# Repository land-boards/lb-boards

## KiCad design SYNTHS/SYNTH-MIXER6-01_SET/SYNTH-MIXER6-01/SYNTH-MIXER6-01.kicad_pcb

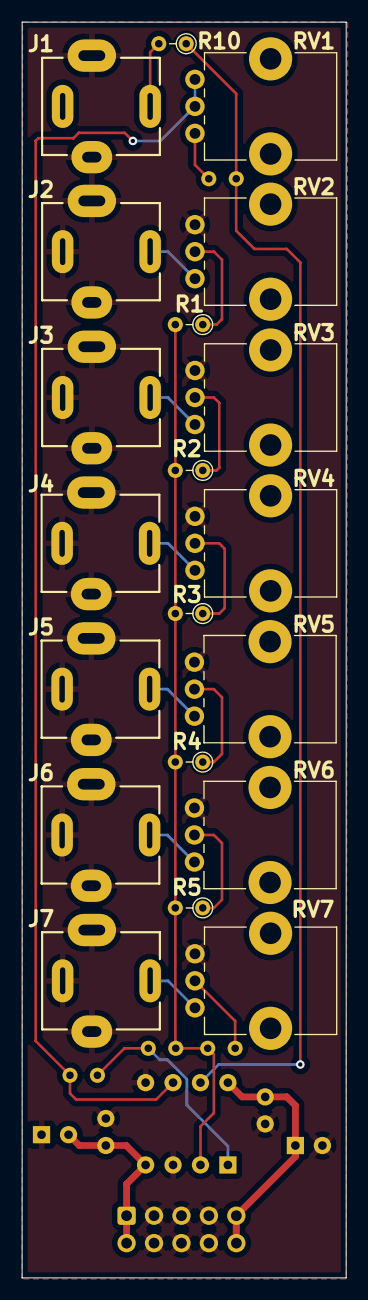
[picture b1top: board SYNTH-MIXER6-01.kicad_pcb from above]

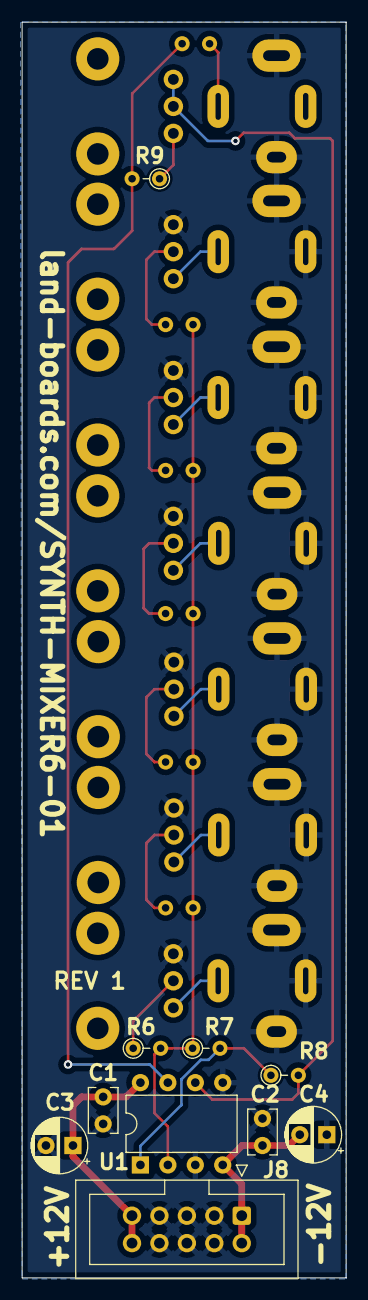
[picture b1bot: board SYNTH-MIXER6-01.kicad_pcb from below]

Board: 2 copper layers, 30.0 x 116.2 mm, 30 parts (10 on the bottom side), 21 nets.

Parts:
C1, C2: 0.1uF; C_Rect_L4.0mm_W2.5mm_P2.50mm
C3, C4: 10uF; CP_Radial_D5.0mm_P2.50mm
J1, J2, J3, J4, J5, J6, J7: PJ-301BM; Jack_3.5mm_QingPu_WQP-PJ301BM_Vertical
J8: Conn_02x05; IDC-Header_2x05_P2.54mm_Vertical
R1, R2, R3, R4, R5, R6, R7: 100K; R_Axial_DIN0204_L3.6mm_D1.6mm_P2.54mm_Vertical
R8: 22K; R_Axial_DIN0204_L3.6mm_D1.6mm_P2.54mm_Vertical
R9: 4.7K; R_Axial_DIN0204_L3.6mm_D1.6mm_P2.54mm_Vertical
R10: 1K; R_Axial_DIN0204_L3.6mm_D1.6mm_P2.54mm_Vertical
RV1, RV2, RV3, RV4, RV5, RV6, RV7: 10K; Potentiometer_Bourns_PTV09A-1_Single_Vertical
U1: TL072; DIP-8_W7.62mm

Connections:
+12V: C1.1, C3.1, J8.9, J8.10, U1.8 (V+)
-12V: C2.2, C4.2, J8.1, J8.2, U1.4 (V-)
/OUT: J1.T, R10.2
/POTWIPER_1: R1.1, RV2.2
/POTWIPER_2: R2.1, RV3.2
/POTWIPER_3: R3.1, RV4.2
/POTWIPER_4: R4.1, RV5.2
/POTWIPER_5: R5.1, RV6.2
/POTWIPER_6: R6.1, RV7.2
/VI_1: J2.T, RV2.1
/VI_2: J3.T, RV3.1
/VI_3: J4.T, RV4.1
/VI_4: J5.T, RV5.1
/VI_5: J6.T, RV6.1
/VI_6: J7.T, RV7.1
/VO: R9.2, R10.1, U1.7
/VOL1: R9.1, RV1.1
/VOL2: R8.2, RV1.2, RV1.3, U1.6 (-)
/VSUM: R1.2, R2.2, R3.2, R4.2, R5.2, R6.2, R7.1, U1.2 (-)
GND: C1.2, C2.1, C3.2, C4.1, J1.S, J2.S, J2.TN, J3.S, J3.TN, J4.S, J4.TN, J5.S, J5.TN, J6.S, J6.TN, J7.S, J7.TN, J8.3, J8.4, J8.5, J8.6, J8.7, J8.8, RV2.3, RV3.3, RV4.3, RV5.3, RV6.3, RV7.3, U1.3 (+), U1.5 (+)
unnamed: R7.2, R8.1, U1.1

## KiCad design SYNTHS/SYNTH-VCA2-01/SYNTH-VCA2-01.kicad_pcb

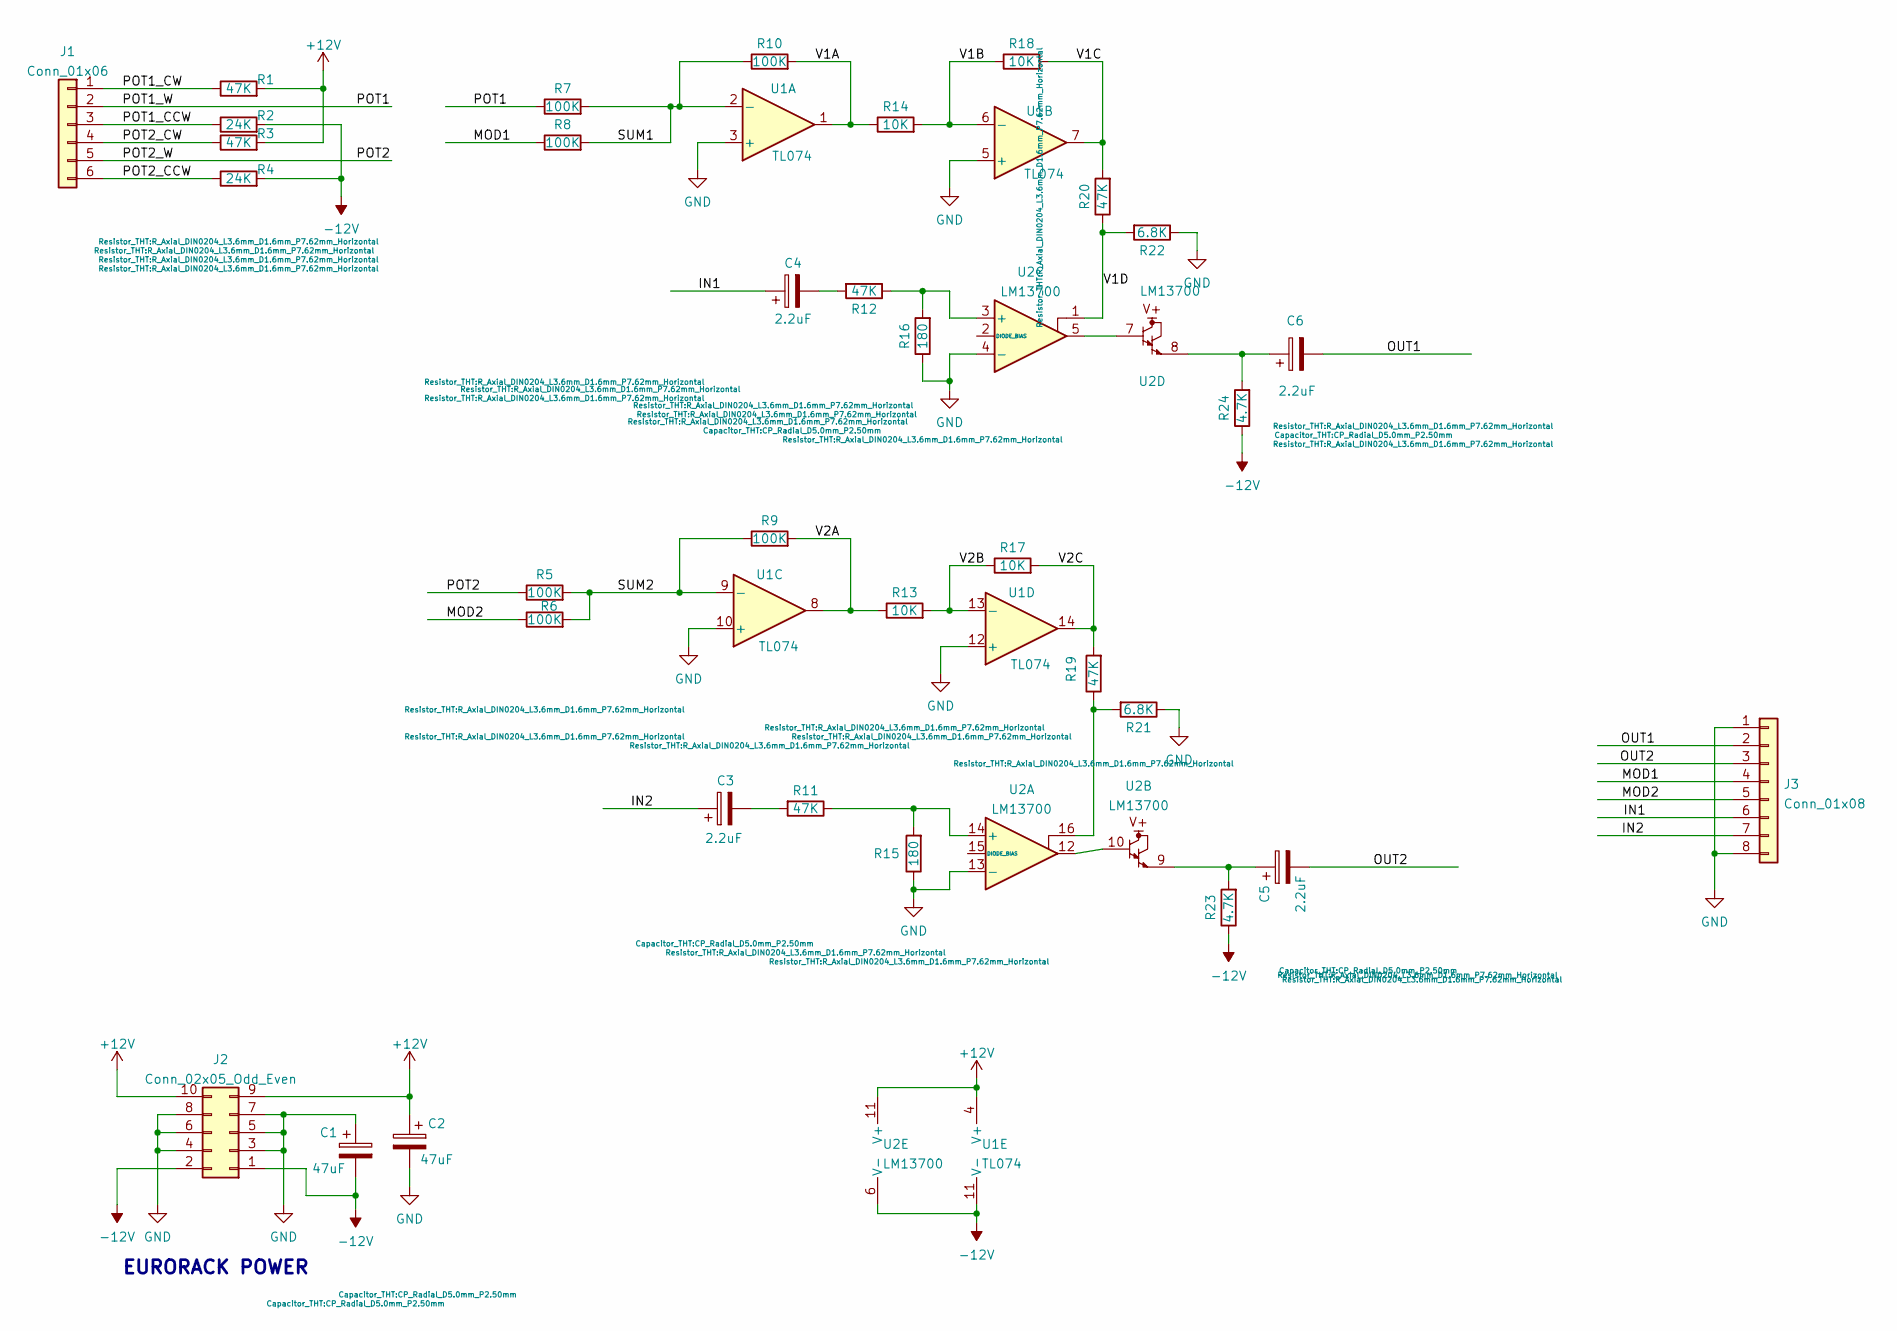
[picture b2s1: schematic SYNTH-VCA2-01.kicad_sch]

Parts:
C1, C2: 47uF; CP_Radial_D5.0mm_P2.50mm
C3, C4, C5, C6: 2.2uF; CP_Radial_D5.0mm_P2.50mm
J1: Conn_01x06; PinSocket_1x06_P2.54mm_Vertical
J2: Conn_02x05_Odd_Even; IDC-Header_2x05_P2.54mm_Vertical
J3: Conn_01x08; PinSocket_1x08_P2.54mm_Vertical
R1, R3, R11, R12, R19, R20: 47K; R_Axial_DIN0204_L3.6mm_D1.6mm_P7.62mm_Horizontal
R2, R4: 24K; R_Axial_DIN0204_L3.6mm_D1.6mm_P7.62mm_Horizontal
R5, R6, R7, R8, R9, R10: 100K; R_Axial_DIN0204_L3.6mm_D1.6mm_P7.62mm_Horizontal
R13, R14, R17, R18: 10K; R_Axial_DIN0204_L3.6mm_D1.6mm_P7.62mm_Horizontal
R15, R16: 180; R_Axial_DIN0204_L3.6mm_D1.6mm_P7.62mm_Horizontal
R21, R22: 6.8K; R_Axial_DIN0204_L3.6mm_D1.6mm_P7.62mm_Horizontal
R23, R24: 4.7K; R_Axial_DIN0204_L3.6mm_D1.6mm_P7.62mm_Horizontal
U1: TL074
U2: LM13700

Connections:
+12V: C2.1, J2.9, J2.10, R1.2, R3.2, U1.4 (V+), U2.11 (V+)
-12V: C1.2, J2.1, J2.2, R2.2, R4.2, R23.1, R24.1, U1.11 (V-), U2.6 (V-)
/IN1: C4.1, J3.6
/IN2: C3.1, J3.7
/MOD1: J3.4, R8.1
/MOD2: J3.5, R6.1
/OUT1: C6.2, J3.2
/OUT2: C5.2, J3.3
/POT1: J1.2, R7.1
/POT1_CCW: J1.3, R2.1
/POT1_CW: J1.1, R1.1
/POT2: J1.5, R5.1
/POT2_CCW: J1.6, R4.1
/POT2_CW: J1.4, R3.1
/SUM1: R7.2, R8.2, R10.1, U1.2 (-)
/SUM2: R5.2, R6.2, R9.1, U1.9 (-)
/V1A: R10.2, R14.1, U1.1
/V1B: R14.2, R18.1, U1.6 (-)
/V1C: R18.2, R20.2, U1.7
/V1D: R20.1, R22.2, U2.1
/V2A: R9.2, R13.1, U1.8
/V2B: R13.2, R17.1, U1.13 (-)
/V2C: R17.2, R19.2, U1.14
GND: C1.1, C2.2, J2.3, J2.4, J2.5, J2.6, J2.7, J2.8, J3.1, J3.8, R15.1, R16.1, R21.1, R22.1, U1.3 (+), U1.5 (+), U1.10 (+), U1.12 (+), U2.4 (-), U2.13 (-)
unnamed: C3.2, R11.2
unnamed: C4.2, R12.2
unnamed: C5.1, R23.2, U2.9
unnamed: C6.1, R24.2, U2.8
unnamed: R12.1, R16.2, U2.3 (+)
unnamed: R11.1, R15.2, U2.14 (+)
unnamed: R19.1, R21.2, U2.16
unnamed: U2.5, U2.7
unnamed: U2.10, U2.12

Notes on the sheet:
EURORACK POWER

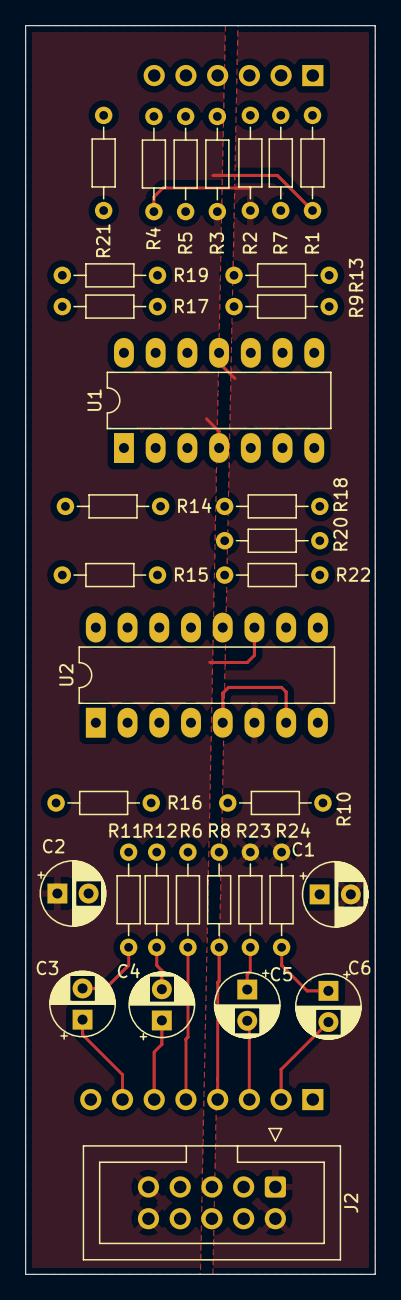
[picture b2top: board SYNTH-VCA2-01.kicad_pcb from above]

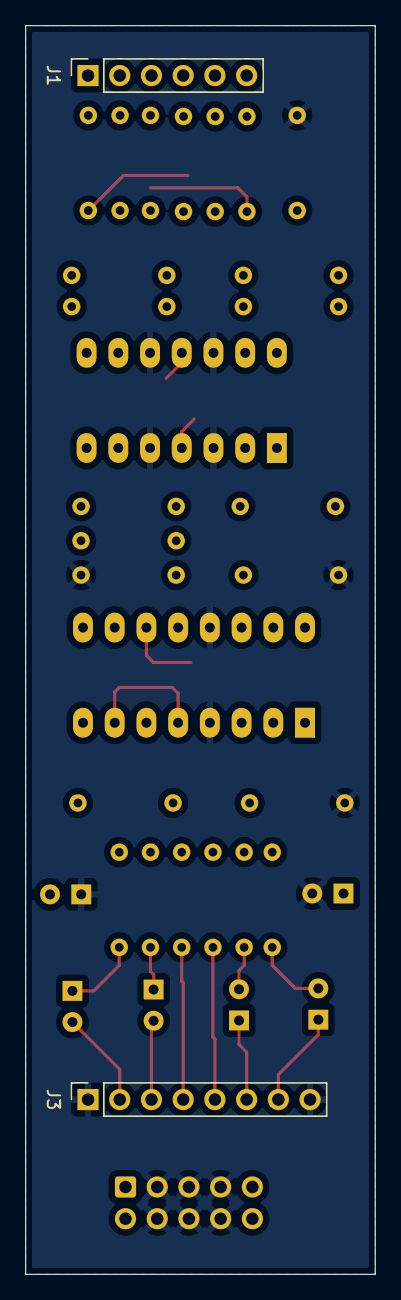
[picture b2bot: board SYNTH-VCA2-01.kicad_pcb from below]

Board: 2 copper layers, 28.0 x 100.0 mm, 35 parts (2 on the bottom side), 33 nets.

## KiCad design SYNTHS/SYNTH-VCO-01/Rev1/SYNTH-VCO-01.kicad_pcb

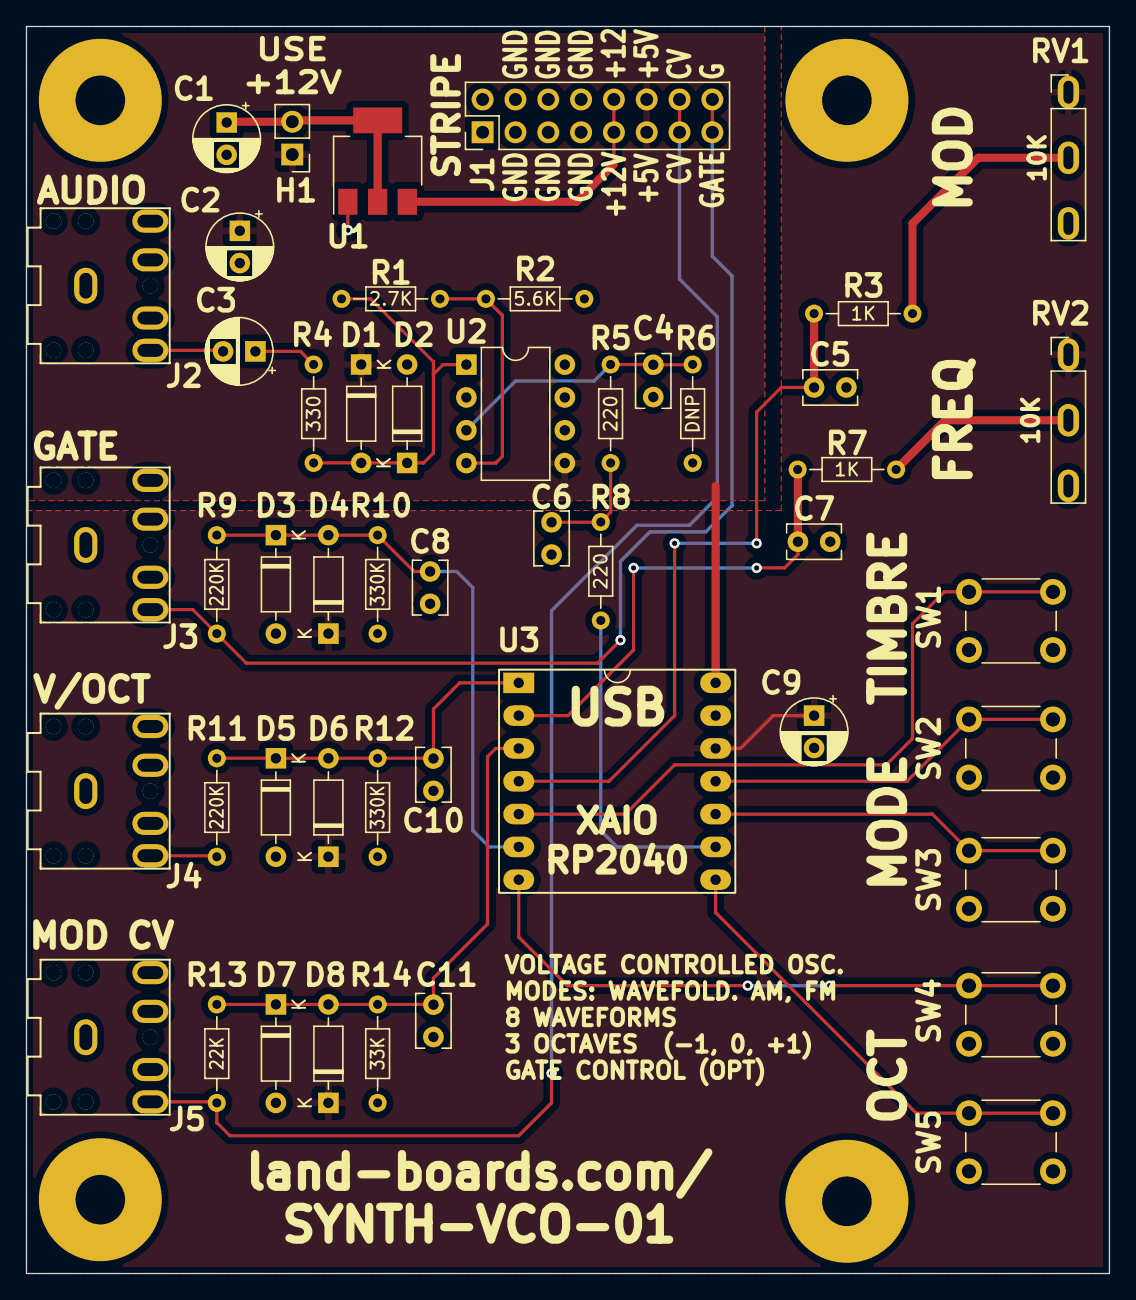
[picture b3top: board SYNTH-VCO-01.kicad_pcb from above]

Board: 2 copper layers, 83.8 x 96.5 mm, 53 parts (0 on the bottom side), 27 nets.

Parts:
C1, C2, C3, C9: 10uF; CP_Radial_D5.0mm_P2.50mm
C4, C6: 10nF; C_Rect_L4.0mm_W2.5mm_P2.50mm
C5, C7: 0.1uF; C_Rect_L4.0mm_W2.5mm_P2.50mm
C8, C10, C11: 0.01uF; C_Rect_L4.0mm_W2.5mm_P2.50mm
D1, D2, D3, D4, D5, D6, D7, D8: BAT41; D_DO-35_SOD27_P7.62mm_Horizontal
H1: Conn_01x02; PinHeader_1x02_P2.54mm_Vertical
J1: Conn_02x08_Odd_Even; PinHeader_2x08_P2.54mm_Vertical
J2, J3, J4, J5: AudioJack3; Jack_3.5mm_CUI_SJ1-3523N_Horizontal
MTG1, MTG2, MTG3, MTG4: MountingHole; MTG-6-32
R1: 2.7K; R_Axial_DIN0204_L3.6mm_D1.6mm_P7.62mm_Horizontal
R2: 5.6K; R_Axial_DIN0204_L3.6mm_D1.6mm_P7.62mm_Horizontal
R3, R7: 1K; R_Axial_DIN0204_L3.6mm_D1.6mm_P7.62mm_Horizontal
R4: 330; R_Axial_DIN0204_L3.6mm_D1.6mm_P7.62mm_Horizontal
R5, R8: 220; R_Axial_DIN0204_L3.6mm_D1.6mm_P7.62mm_Horizontal
R6: DNP; R_Axial_DIN0204_L3.6mm_D1.6mm_P7.62mm_Horizontal
R9, R11: 220K; R_Axial_DIN0204_L3.6mm_D1.6mm_P7.62mm_Horizontal
R10, R12: 330K; R_Axial_DIN0204_L3.6mm_D1.6mm_P7.62mm_Horizontal
R13: 22K; R_Axial_DIN0204_L3.6mm_D1.6mm_P7.62mm_Horizontal
R14: 33K; R_Axial_DIN0204_L3.6mm_D1.6mm_P7.62mm_Horizontal
RV1, RV2: 10K; Pot3
SW1, SW2, SW3, SW4, SW5: SW_Push; SW_PUSH_6mm_H8.5mm
U1: AZ1117-5; SOT-223
U2: MCP6232; DIP-8_W7.62mm
U3: XIAO_RP2040; QT_Py

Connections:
+3V3: C9.1, D4.1 (K), D6.1 (K), D8.1 (K), RV1.1, RV2.1, U3.12 (3.3V)
+5V: C2.1, D1.1 (K), H1.1, J1.11, J1.12, U2.5 (V+), U3.14 (5V)
+12V: J1.9, J1.10, U1.3 (VIN)
/AUD_OUT: C3.1, R4.1
/CV: J1.13, J1.14, J5.T, R13.1
/FREQ_POT: C7.1, R7.2, U3.2 (D1/P27)
/GATE: J1.15, J1.16, J3.T, R9.1
/GATE_CTL: C8.1, D3.1 (K), D4.2 (A), R9.2, R10.2, U3.6 (D5/SCL/P7)
/MODE_DN_PB: SW3.1, U3.10 (D9/MISO/P4)
/MODE_UP_PB: SW2.1, U3.11 (D10/MOSI/P3)
/MOD_CV: C11.1, D7.1 (K), D8.2 (A), R13.2, R14.2, U3.3 (D2/P28)
/MOD_POT: C5.1, R3.2, U3.4 (D3/P29)
/OCT_DN_PB: SW5.1, U3.8 (D7/RX/P1)
/OCT_UP_PB: SW4.2, U3.7 (D6/TX/P0)
/PRE_FILT: C4.1, R5.2, R6.1, U2.3 (+)
/TIMBRE_PB: SW1.2, U3.5 (D4/SDA/P6)
/VPEROCT_CV: C10.1, D5.1 (K), D6.2 (A), R11.2, R12.2, U3.1 (D0/P26)
/V_OCT: J4.T, R11.1
/WAV: R8.1, U3.9 (D8/SCK/P2)
GND: C1.2, C2.2, C4.2, C5.2, C6.2, C7.2, C8.2, C9.2, C10.2, C11.2, D2.2 (A), D3.2 (A), D5.2 (A), D7.2 (A), J1.3, J1.4, J1.5, J1.6, J1.7, J1.8, J2.S, J3.S, J4.S, J5.S, R2.1, R6.2, R10.1, R12.1, R14.1, RV1.3, RV2.3, SW1.1, SW2.2, SW3.2, SW4.1, SW5.2, U1.1 (GND), U2.2 (V-), U3.13 (GND)
unnamed: C1.1, H1.2, U1.2 (VO), U1.4 (VO)
unnamed: C3.2, J2.T
unnamed: C6.1, R5.1, R8.2
unnamed: D1.2 (A), D2.1 (K), R1.2, R4.2, U2.1
unnamed: R1.1, R2.2, U2.4 (-)
unnamed: R3.1, RV1.2
unnamed: R7.1, RV2.2

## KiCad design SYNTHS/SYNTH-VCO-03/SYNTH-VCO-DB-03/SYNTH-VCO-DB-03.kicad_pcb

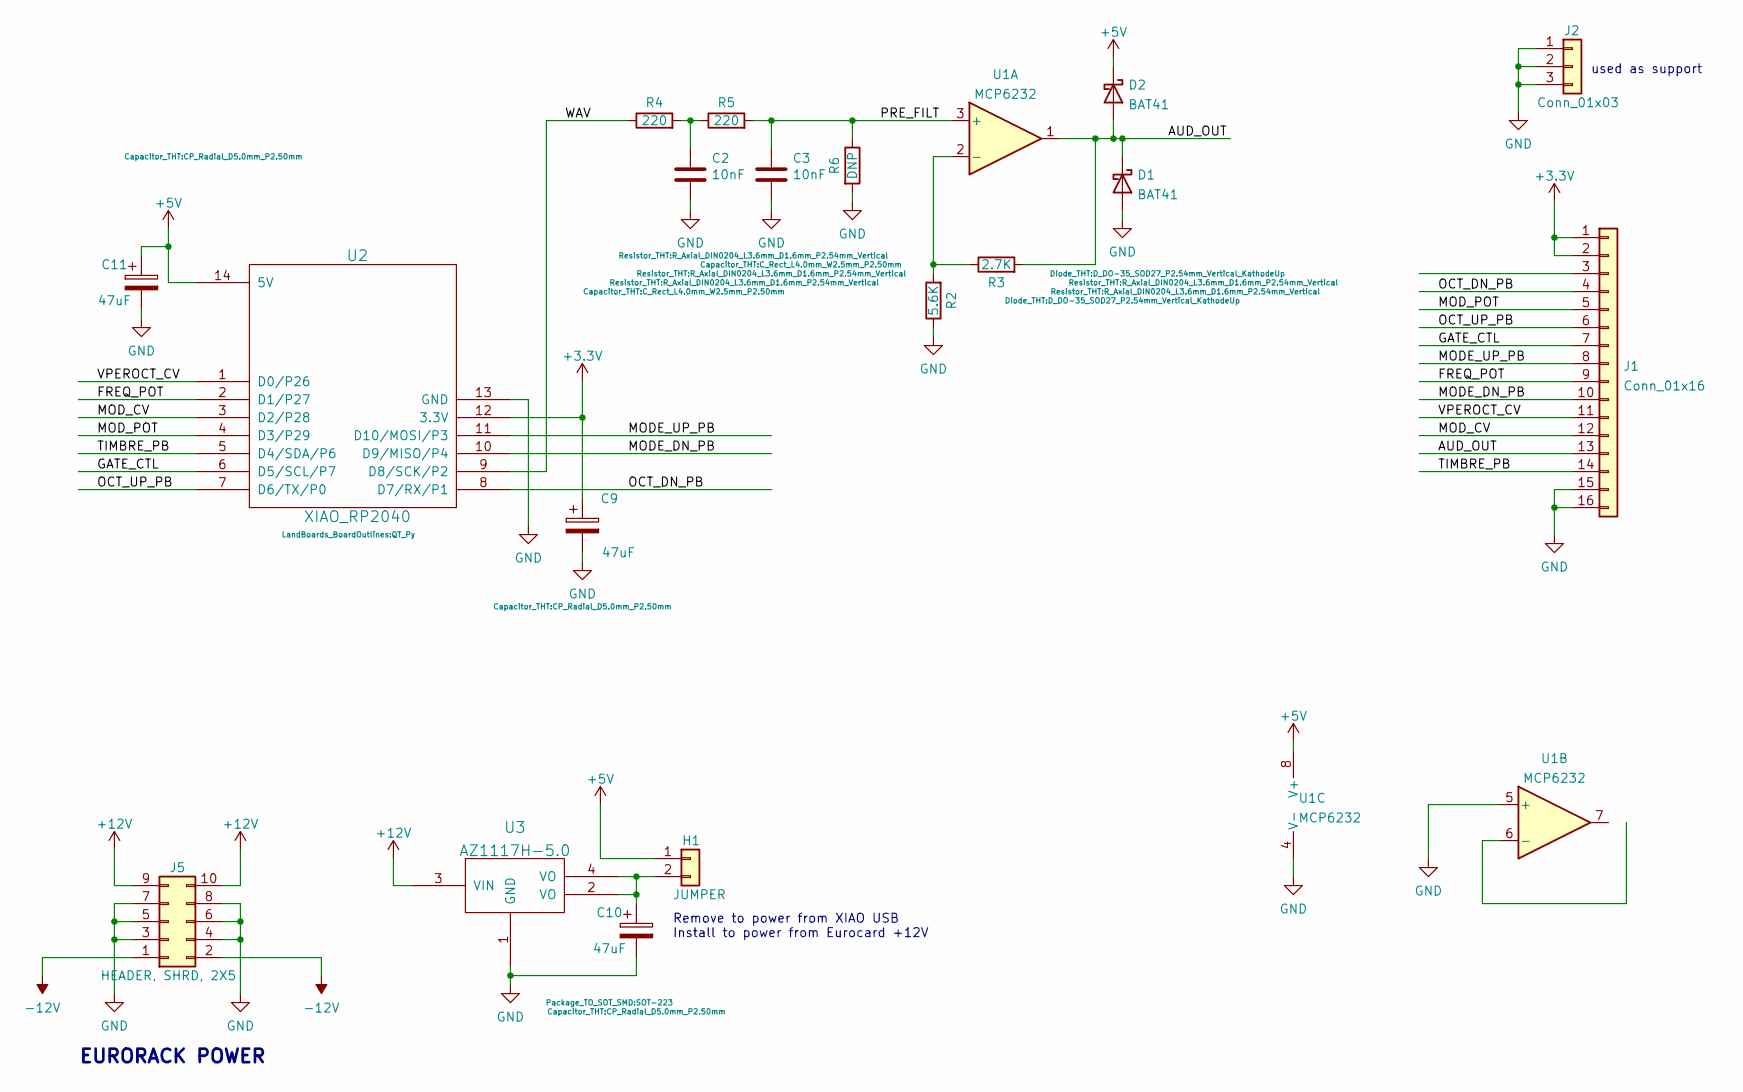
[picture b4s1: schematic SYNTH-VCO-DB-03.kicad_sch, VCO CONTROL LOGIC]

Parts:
C2, C3: 10nF; C_Rect_L4.0mm_W2.5mm_P2.50mm
C9, C10, C11: 47uF; CP_Radial_D5.0mm_P2.50mm
D1, D2: BAT41; D_DO-35_SOD27_P2.54mm_Vertical_KathodeUp
H1: JUMPER; PinHeader_1x02_P2.54mm_Vertical
J1: Conn_01x16; PinHeader_2x08_P2.54mm_Vertical
J2: Conn_01x03; PinHeader_1x03_P2.54mm_Vertical
J5: HEADER, SHRD, 2X5; IDC-Header_2x05_P2.54mm_Vertical
R2: 5.6K; R_Axial_DIN0204_L3.6mm_D1.6mm_P2.54mm_Vertical
R3: 2.7K; R_Axial_DIN0204_L3.6mm_D1.6mm_P2.54mm_Vertical
R4, R5: 220; R_Axial_DIN0204_L3.6mm_D1.6mm_P2.54mm_Vertical
R6: DNP; R_Axial_DIN0204_L3.6mm_D1.6mm_P2.54mm_Vertical
U1: MCP6232; DIP-8_W7.62mm
U2: XIAO_RP2040; QT_Py
U3: AZ1117H-5.0; SOT-223

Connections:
+3V3: C9.1, J1.1, J1.2, U2.12 (3.3V)
+5V: C11.1, D2.1 (K), H1.1, U1.8 (V+), U2.14 (5V)
+12V: J5.9, J5.10, U3.3 (VIN)
-12V: J5.1, J5.2
/AUD_OUT: D1.1 (K), D2.2 (A), J1.13, R3.2, U1.1
/FREQ_POT: J1.9, U2.2 (D1/P27)
/GATE_CTL: J1.7, U2.6 (D5/SCL/P7)
/MODE_DN_PB: J1.10, U2.10 (D9/MISO/P4)
/MODE_UP_PB: J1.8, U2.11 (D10/MOSI/P3)
/MOD_CV: J1.12, U2.3 (D2/P28)
/MOD_POT: J1.5, U2.4 (D3/P29)
/OCT_DN_PB: J1.4, U2.8 (D7/RX/P1)
/OCT_UP_PB: J1.6, U2.7 (D6/TX/P0)
/PRE_FILT: C3.1, R5.2, R6.1, U1.3 (+)
/TIMBRE_PB: J1.14, U2.5 (D4/SDA/P6)
/VPEROCT_CV: J1.11, U2.1 (D0/P26)
/WAV: R4.1, U2.9 (D8/SCK/P2)
GND: C2.2, C3.2, C9.2, C10.2, C11.2, D1.2 (A), J1.15, J1.16, J2.1, J2.2, J2.3, J5.3, J5.4, J5.5, J5.6, J5.7, J5.8, R2.1, R6.2, U1.4 (V-), U1.5 (+), U2.13 (GND), U3.1 (GND)
unnamed: C2.1, R4.2, R5.1
unnamed: C10.1, H1.2, U3.2 (VO), U3.4 (VO)
unnamed: R2.2, R3.1, U1.2 (-)

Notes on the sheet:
used as support
EURORACK POWER
Remove to power from XIAO USB Install to power from Eurocard +12V

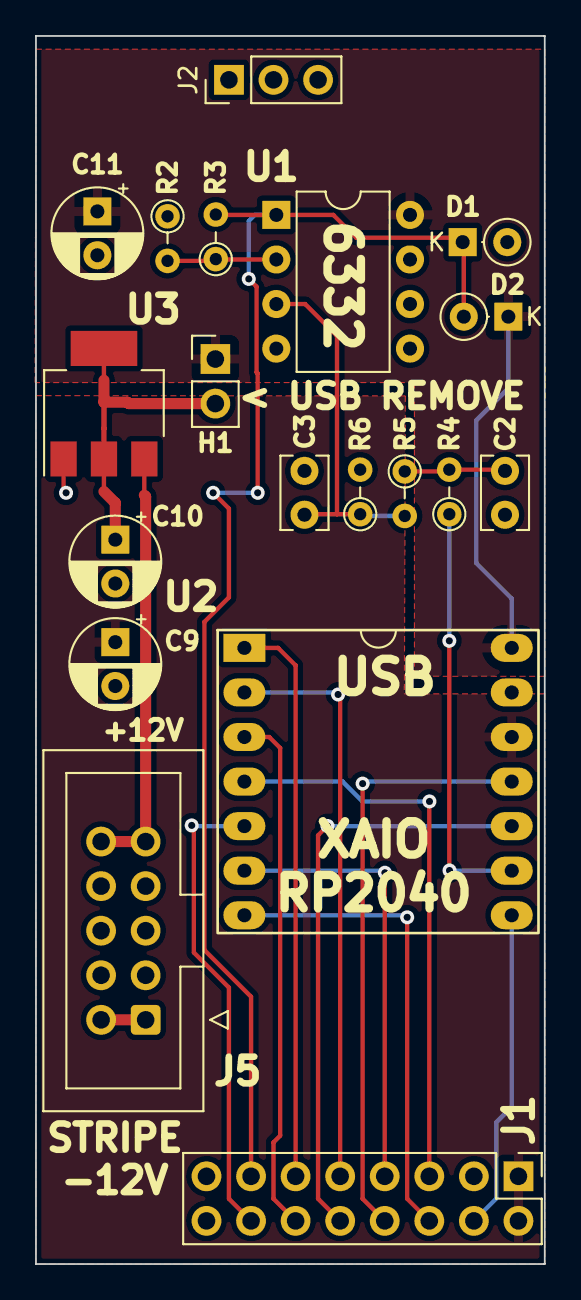
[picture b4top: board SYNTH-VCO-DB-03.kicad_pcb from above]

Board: 2 copper layers, 29.0 x 70.0 mm, 19 parts (0 on the bottom side), 21 nets.

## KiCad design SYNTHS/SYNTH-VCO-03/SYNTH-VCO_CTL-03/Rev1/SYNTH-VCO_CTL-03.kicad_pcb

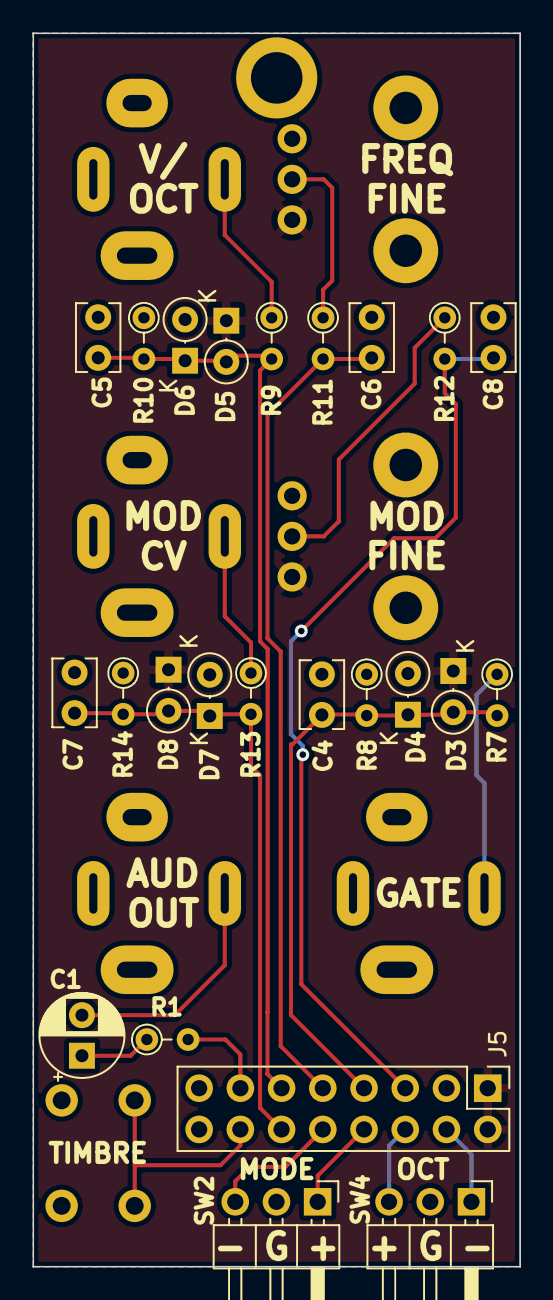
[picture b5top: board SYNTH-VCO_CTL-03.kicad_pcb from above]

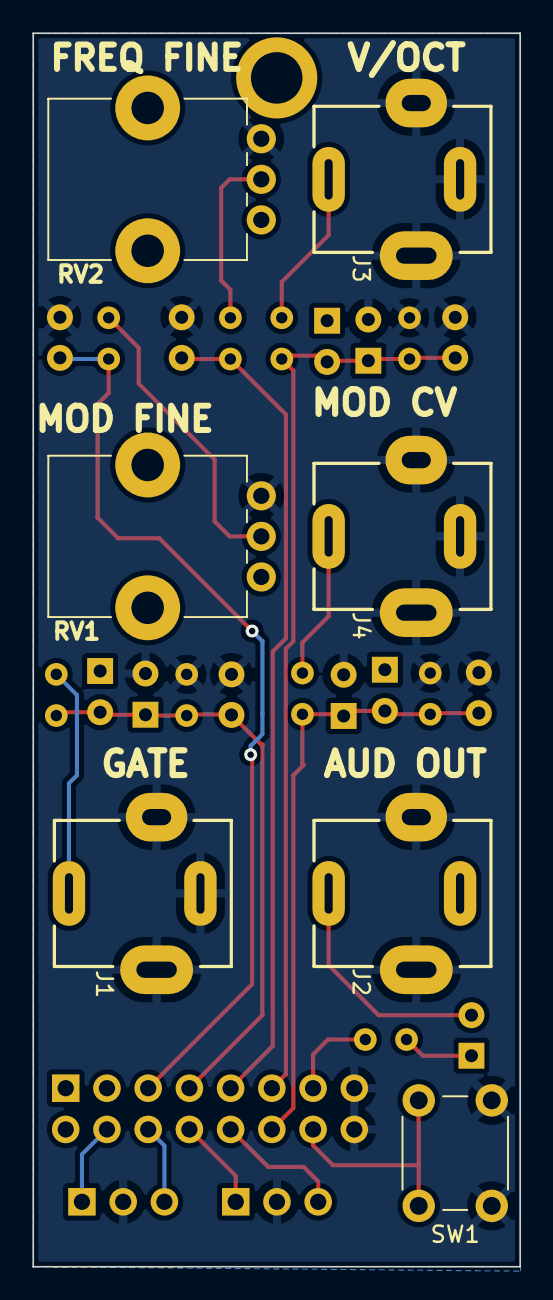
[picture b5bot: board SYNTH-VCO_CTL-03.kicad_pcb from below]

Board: 2 copper layers, 30.0 x 76.0 mm, 32 parts (7 on the bottom side), 20 nets.

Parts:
C1: 47uF; CP_Radial_D5.0mm_P2.50mm
C4, C5, C7: 0.01uF; C_Rect_L4.0mm_W2.5mm_P2.50mm
C6, C8: 0.1uF; C_Rect_L4.0mm_W2.5mm_P2.50mm
D3, D4, D5, D6, D7, D8: BAT41; D_DO-35_SOD27_P2.54mm_Vertical_KathodeUp
J1, J2, J3, J4: PJ-301BM; Jack_3.5mm_QingPu_WQP-PJ301BM_Vertical
J5: Conn_01x16; PinHeader_2x08_P2.54mm_Vertical
MTG1: MTG_HOLE; MTG-4-40-SMALL
R1: 330; R_Axial_DIN0204_L3.6mm_D1.6mm_P2.54mm_Vertical
R7, R9: 220K; R_Axial_DIN0204_L3.6mm_D1.6mm_P2.54mm_Vertical
R8, R10: 330K; R_Axial_DIN0204_L3.6mm_D1.6mm_P2.54mm_Vertical
R11, R12: 1K; R_Axial_DIN0204_L3.6mm_D1.6mm_P2.54mm_Vertical
R13: 22K; R_Axial_DIN0204_L3.6mm_D1.6mm_P2.54mm_Vertical
R14: 33K; R_Axial_DIN0204_L3.6mm_D1.6mm_P2.54mm_Vertical
RV1, RV2: 10K; Potentiometer_Bourns_PTV09A-1_Single_Vertical
SW1: SW_Push; SW_PUSH_6mm_H5mm
SW2, SW4: SW_SPDT_MSM; PinHeader_1x03_P2.54mm_Horizontal

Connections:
+3V3: D3.1 (K), D5.1 (K), D8.1 (K), J5.1, J5.2, RV1.3, RV2.3
/AUD_OUT: J5.13, R1.2
/CV: J4.T, R13.1
/FREQ_FINE: R11.1, RV2.2
/FREQ_POT: C6.1, J5.9, R11.2
/GATE: J1.T, R7.1
/GATE_CTL: C4.1, D3.2 (A), D4.1 (K), J5.7, R7.2, R8.2
/MODE_DN_PB: J5.10, SW2.3
/MODE_UP_PB: J5.8, SW2.1
/MOD_CV: C7.1, D7.1 (K), D8.2 (A), J5.12, R13.2, R14.2
/MOD_FINE: R12.1, RV1.2
/MOD_POT: C8.1, J5.5, R12.2
/OCT_DN_PB: J5.4, SW4.1
/OCT_UP_PB: J5.6, SW4.3
/TIMBRE_PB: J5.14, SW1.2
/VPEROCT_CV: C5.1, D5.2 (A), D6.1 (K), J5.11, R9.2, R10.2
/V_OCT: J3.T, R9.1
GND: C4.2, C5.2, C6.2, C7.2, C8.2, D4.2 (A), D6.2 (A), D7.2 (A), J1.S, J1.TN, J2.S, J3.S, J3.TN, J4.S, J4.TN, J5.15, J5.16, R8.1, R10.1, R14.1, RV1.1, RV2.1, SW1.1, SW2.2, SW4.2
unnamed: C1.1, R1.1
unnamed: C1.2, J2.T
